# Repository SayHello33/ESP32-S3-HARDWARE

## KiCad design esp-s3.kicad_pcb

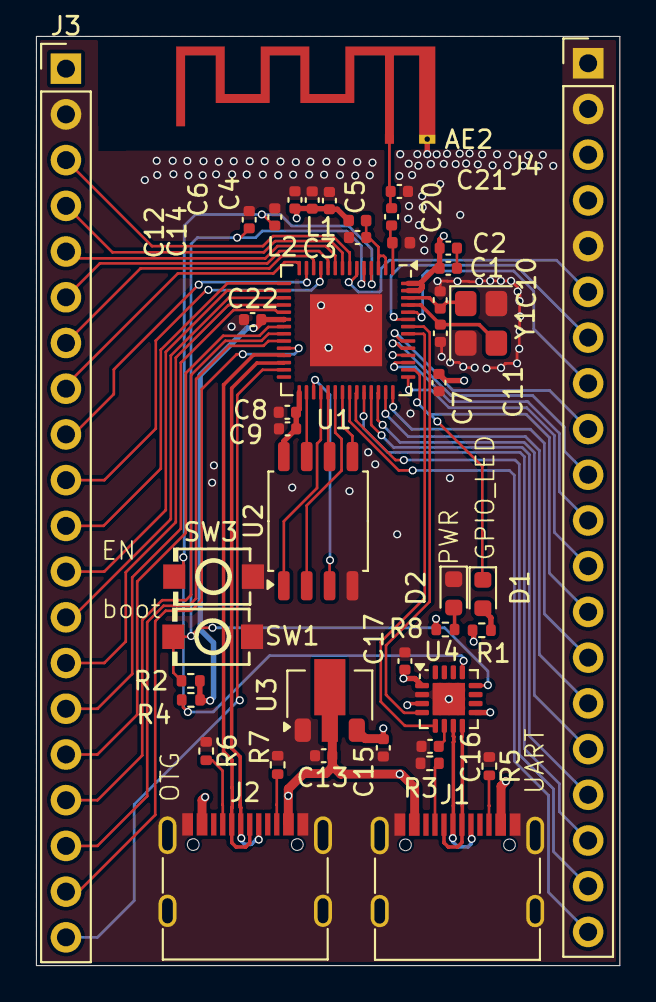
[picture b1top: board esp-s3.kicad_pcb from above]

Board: 4 copper layers, 32.4 x 51.6 mm, 44 parts (0 on the bottom side), 64 nets.

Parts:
AE2: Antenna_Shield; Texas_SWRA117D_2.4GHz_Left
C1: 10nf; C_0402_1005Metric
C2, C4, C9, C12, C14, C17: 1uf; C_0402_1005Metric
C3, C5, C7, C8, C16, C22: 100nf; C_0402_1005Metric
C6, C13, C15: 10uf; C_0402_1005Metric
C10, C11: 10pf; C_0402_1005Metric
C20: 4.7PF; C_0402_1005Metric
C21: 2.4pf; C_0402_1005Metric
D1, D2: NCD0603R1; LED_0603_1608Metric
J1, J2: USB1; USB_C_Receptacle_G-Switch_GT-USB-7010ASV
J3, J4: Conn_01x15_Pin; PinHeader_1x20_P2.54mm_Vertical
L1: 2nH; L_0402_1005Metric
L2: 2.4nh; L_0402_1005Metric
R1, R8: 100Ω; R_0402_1005Metric
R2, R4: 4.7kΩ; R_0402_1005Metric
R3, R5, R6, R7: 5.1K; R_0402_1005Metric
SW1, SW3: SW_Push; SW-SMD_L3.9-W3.0-P4.45
U1: ESP32-S3; QFN-56-1EP_7x7mm_P0.4mm_EP4x4mm
U2: W25Q16JVSS; SOIC-8_5.3x5.3mm_P1.27mm
U3: ME6231A33PG; SOT-89-3
U4: CH343P; WCH_QFN-16-1EP_3x3mm_P0.5mm_EP1.8x1.8mm
Y1: Crystal_GND24; Crystal_SMD_3225-4Pin_3.2x2.5mm

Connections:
/ESP32S3/VDD3P3: C3.1, L1.1, U1.2 (VDD3P3), U1.3 (VDD3P3)
CHIP_PU: C14.1, R4.1, SW3.2, U1.4 (CHIP_PU), U4.13 (~RTS)
GND: AE2.2 (Shield), C3.2, C4.2, C5.2, C6.2, C7.2, C8.2, C9.2, C10.2, C11.2, C12.2, C13.2, C14.2, C15.2, C16.1, C17.1, C21.1, C22.1, D2.1 (K), J1.A1 (GND), J1.A12 (GND), J1.B1 (GND), J1.B12 (GND), J1.S1 (SHIELD), J2.A1 (GND), J2.A12 (GND), J2.B1 (GND), J2.B12 (GND), J2.S1 (SHIELD), J3.2, J4.1, J4.2, J4.5, L2.2, R3.1, R5.1, R6.1, R7.1, SW1.1, SW3.1, U1.57 (GND), U2.4 (GND), U3.1 (V_{SS}), U4.2 (GND), U4.17 (GND_EPAD), Y1.2, Y1.4
GPIO0: C12.1, R2.1, SW1.2, U1.5 (GPIO0), U4.12 (~DTR)
GPIO1: J4.6, U1.6 (GPIO1)
GPIO2: J3.3, U1.7 (GPIO2)
GPIO3: J3.4, U1.8 (GPIO3)
GPIO4: J3.5, U1.9 (GPIO4)
GPIO5: J3.6, U1.10 (GPIO5)
GPIO6: J3.10, U1.11 (GPIO6)
GPIO7: J3.7, U1.12 (GPIO7)
GPIO8: J3.9, U1.13 (GPIO8)
GPIO9: J3.8, U1.14 (GPIO9)
GPIO10: J3.11, U1.15 (GPIO10)
GPIO11: J3.12, U1.16 (GPIO11)
GPIO12: J3.13, U1.17 (GPIO12)
GPIO13: J3.14, U1.18 (GPIO13)
GPIO14: J3.15, U1.19 (GPIO14)
GPIO15: J3.16, U1.21 (XTAL_32K_P)
GPIO16: J3.17, U1.22 (XTAL_32K_N)
GPIO17: J3.18, U1.23 (GPIO17)
GPIO18: J3.19, U1.24 (GPIO18)
GPIO21: J3.20, U1.27 (GPIO21)
GPIO33: J4.18, U1.38 (GPIO33)
GPIO34: J4.17, U1.39 (GPIO34)
GPIO35: J4.16, U1.40 (GPIO35)
GPIO36: J4.15, U1.41 (GPIO36)
GPIO37: J4.14, U1.42 (GPIO37)
GPIO38: J4.12, U1.43 (GPIO38)
GPIO39: D1.1 (K), J4.13, U1.44 (MTCK)
GPIO40: J4.11, U1.45 (MTDO)
GPIO41: J4.10, U1.47 (MTDI)
GPIO42: J4.9, U1.48 (MTMS)
GPIO45: J4.7, U1.51 (GPIO45)
GPIO46: J4.8, U1.52 (GPIO46)
GPIO47: J4.19, U1.37 (SPICLK_P)
GPIO48: J4.20, U1.36 (SPICLK_N)
LNA_IN: C20.1, L2.1, U1.1 (LNA_IN)
unnamed: AE2.1 (A), C20.2, C21.2
unnamed: C1.2, C2.2
unnamed: D1.2 (A), R1.2
unnamed: D2.2 (A), R8.2
unnamed: J1.A5 (CC1), R3.2
unnamed: J1.B5 (CC2), R5.2
unnamed: J2.A5 (CC1), R6.2
unnamed: J2.B5 (CC2), R7.2
unnamed: C16.2, U4.6 (V3_{OUT})
RXD: U1.50 (U0RXD), U4.4 (TXD)
SPICLK: U1.33 (SPICLK), U2.6 (CLK)
SPICS0: U1.32 (SPICS0), U2.1 (~CS)
SPID: U1.35 (SPID), U2.5 (DI/IO_{0})
SPIHD: U1.30 (SPIHD), U2.7 (~HOLD/~RESET/IO_{3})
SPIQ: U1.34 (SPIQ), U2.2 (DO/IO_{1})
SPIWP: U1.31 (SPIWP), U2.3 (~WP/IO_{2})
TXD: U1.49 (U0TXD), U4.5 (RXD)
U+: J1.A6 (D+), J1.B6 (D+), U4.7 (UD+)
U-: J1.A7 (D-), J1.B7 (D-), U4.8 (UD-)
USB_D+: J2.A6 (D+), J2.B6 (D+), U1.26 (GPIO20/USB_D+)
USB_D-: J2.A7 (D-), J2.B7 (D-), U1.25 (GPIO19/USB_D-)
VBUS: C13.1, J1.A4 (VBUS), J1.A9 (VBUS), J1.B4 (VBUS), J1.B9 (VBUS), J2.A4 (VBUS), J2.A9 (VBUS), J2.B4 (VBUS), J2.B9 (VBUS), U3.2 (V_{IN}), U4.3 (VDD5), U4.9 (VBUS)
VDD33: C1.1, C2.1, C4.1, C5.1, C6.1, C7.1, C15.1, C17.2, C22.2, J3.1, J4.3, J4.4, L1.2, R1.1, R2.2, R4.2, R8.1, U1.20 (VDD3P3_RTC), U1.46 (VDD3P3_CPU), U1.55 (VDDA), U1.56 (VDDA), U3.3 (V_{OUT}), U4.1 (VIO)
VDDSPI: C8.1, C9.1, U1.29 (VDD_SPI), U2.8 (VCC)
XTAL_N: C11.1, U1.53 (XTAL_N), Y1.3
XTAL_P: C10.1, U1.54 (XTAL_P), Y1.1

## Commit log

2025-07-16 添加引脚标注
2025-07-17 🚀初步完善原理图
2025-07-19 初步完成PCB
2025-07-20 添加pcb丝印
2025-07-20 丝印修改
2025-07-21 修复L3电源层
